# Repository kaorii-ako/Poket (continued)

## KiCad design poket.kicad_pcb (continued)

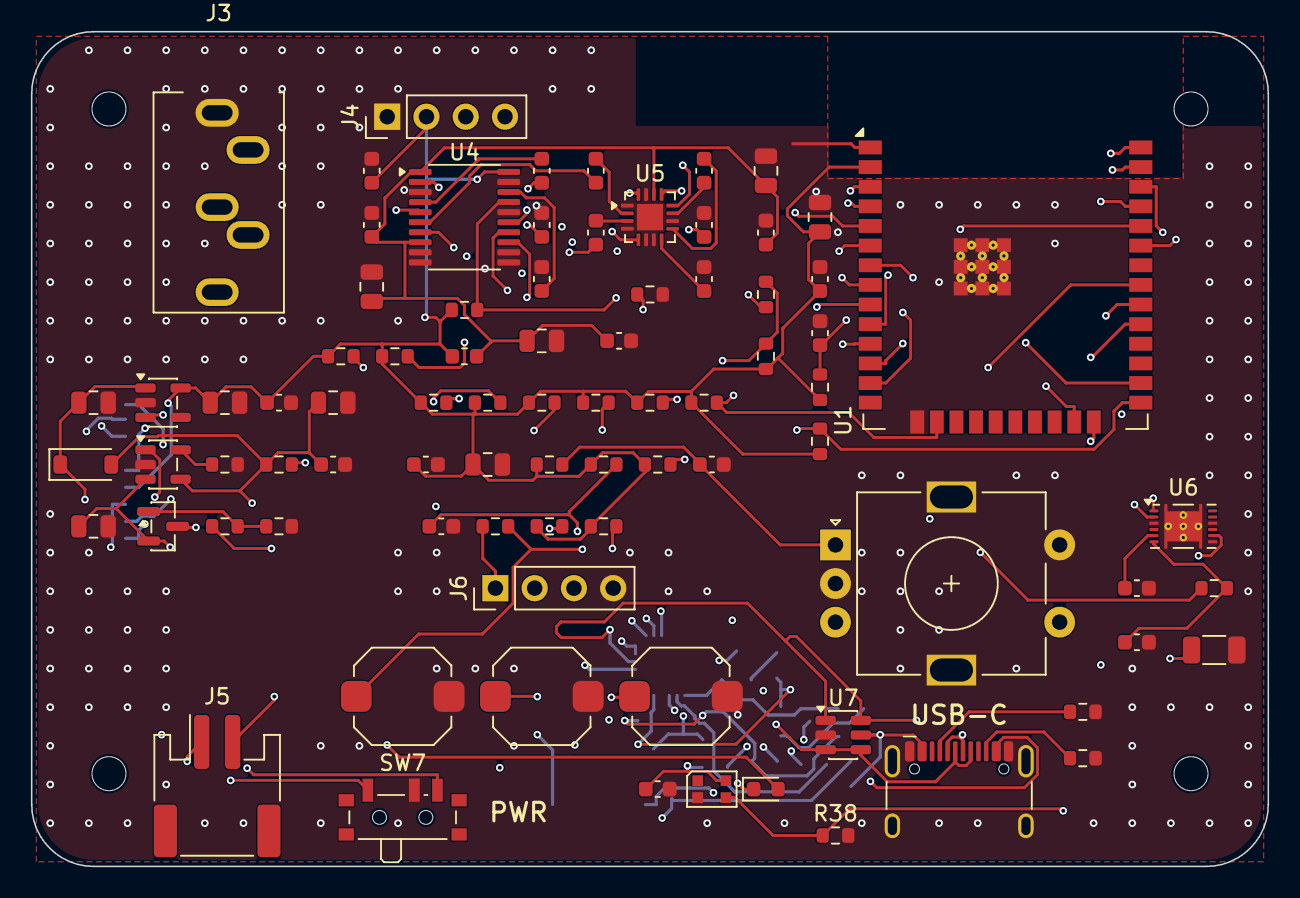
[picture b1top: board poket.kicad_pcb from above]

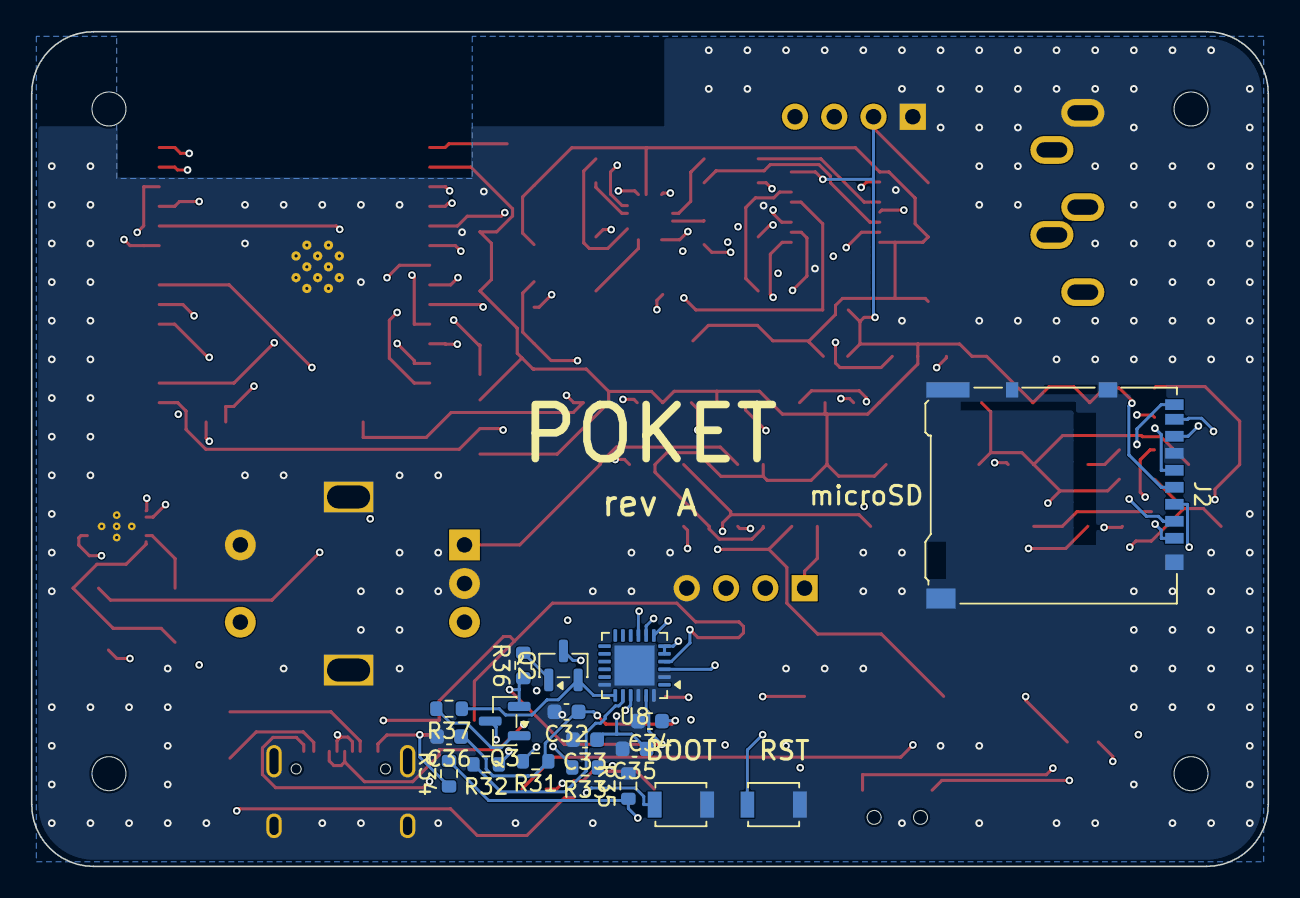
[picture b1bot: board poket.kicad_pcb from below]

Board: 4 copper layers, 80.0 x 54.0 mm, 104 parts (18 on the bottom side), 67 nets.

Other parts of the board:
MH1, MH2, MH3, MH4: MountingHole_2.2mm

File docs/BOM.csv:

Section,Ref,Qty,Value,MPN,Package,Description,Est unit USD,Est ext USD
MCU,U1,1,ESP32-WROOM-32E-N16R2,ESP32-WROOM-32E-N16R2,SMD module,Dual-core MCU + Classic BT/BLE/WiFi radio 16MB flash 2MB in-package PSRAM,3.80,3.80
Audio,U4,1,PCM5102A,PCM5102APWR,TSSOP-20,I2S stereo DAC internal PLL no MCLK needed,2.20,2.20
Audio,U5,1,PAM8908,PAM8908JER,QFN-16 3x3 EP,Stereo headphone amp charge-pump ground-centred output,0.60,0.60
Audio,J3,1,3.5mm TRS,SJ1-3535NG,THT horizontal,3.5mm stereo jack with switched tip for plug detect,0.60,0.60
Power,U2,1,MCP73831-2-OT,MCP73831T-2ACI/OT,SOT-23-5,Single-cell LiPo charger 500mA set by R3,0.65,0.65
Power,U3,1,AP2112K-3.3,AP2112K-3.3TRG1,SOT-23-5,3.3V 600mA LDO with enable,0.20,0.20
Power,U6,1,BQ27441-G1,BQ27441DRZR-G1A,SON-12 2x4mm,Coulomb-counting fuel gauge I2C,2.80,2.80
Power,Q1,1,DMG2301L,DMG2301L,SOT-23,P-channel MOSFET load-share switch,0.20,0.20
Power,D3,1,B5819W,B5819WS,SOD-123,Schottky diode USB-to-VSYS path,0.05,0.05
Power,U7,1,USBLC6-2SC6,USBLC6-2SC6,SOT-23-6,USB ESD protection array,0.25,0.25
Storage,J2,1,microSD,DM3AT-SF-PEJM5,SMD push-push,microSD socket with card-detect switch,1.00,1.00
UI,SW1,1,EC11E,EC11E15244A3,THT vertical H20mm,Rotary encoder with push switch,0.45,0.45
UI,SW2-SW4,3,Tact 6x6x5,TS-1187A-B-A-B,SMD 6x6x5mm,Transport buttons prev/play/next,0.10,0.30
UI,SW5-SW6,2,Tact 3.9x2.9,B3U-1000P,SMD,BOOT and RESET on the underside,0.15,0.30
UI,SW7,1,Slide SPDT,PCM12SMTR,SMD,Power slide switch drives the LDO enable,0.30,0.30
UI,D1,1,WS2812B-2020,WS2812B-2020,PLCC-4 2x2mm,Addressable RGB status LED,0.15,0.15
UI,D2,1,LED green,KT-0603G,0603,Charge status LED,0.03,0.03
Connectors,J1,1,USB-C,HC-TYPE-C-16P-01A,SMD 16P,USB-C receptacle USB 2.0,0.30,0.30
Connectors,J5,1,JST-PH 2pin,S2B-PH-SM4-TB,SMD horizontal,Battery connector,0.15,0.15
Connectors,J4,1,Header 1x4,Generic 2.54mm,THT,OLED module connection,0.05,0.05
Connectors,J6,1,Header 1x4,Generic 2.54mm,THT,UART debug header,0.05,0.05
Passives,FB1,1,600R@100MHz,Generic 0603,0603,Ferrite bead isolating the 3V3A analog rail,0.03,0.03
Passives,C1;C3-C5;C7;C9;C13;C16;C25,9,10uF,Generic X5R 0805 16V,0805,Bulk decoupling,0.03,0.27
Passives,C2;C6;C8;C10;C12;C14;C15;C26-C29,11,100nF,Generic X7R 0603 25V,0603,Bypass,0.01,0.11
Passives,C11;C18-C24,8,1uF,Generic X7R 0603 16V,0603,Charge-pump and coupling caps,0.02,0.16
Passives,C17,1,2.2uF,Generic X7R 0603 16V,0603,DAC charge-pump flying cap,0.02,0.02
Passives,C30;C31,2,10nF,Generic X7R 0603 50V,0603,Encoder RC filter,0.01,0.02
Passives,R1;R2,2,5.1k,Generic 0603 1%,0603,USB-C CC pulldowns,0.01,0.02
Passives,R3,1,2k,Generic 0603 1%,0603,Charge current program 500mA,0.01,0.01
Passives,R4;R23,2,1k,Generic 0603 1%,0603,LED series and fuel-gauge BAT filter,0.01,0.02
Passives,R5;R7;R8;R11-R19;R25-R30,18,10k,Generic 0603 1%,0603,Pull-ups and pull-downs,0.01,0.18
Passives,R6,1,1M,Generic 0603 1%,0603,Load-share gate pulldown,0.01,0.01
Passives,R9;R10,2,4.7k,Generic 0603 1%,0603,I2C pull-ups,0.01,0.02
Passives,R20-R22,3,100k,Generic 0603 1%,0603,Jack detect and battery divider,0.01,0.03
Passives,R24,1,0.01R,Generic 1206 1% 1W,1206,Fuel-gauge sense resistor,0.10,0.10
Off-board,BT1,1,LiPo 402535 400mAh,Generic 402535,4x25x35mm,Single-cell LiPo with protection,5.00,5.00
Off-board,DS1,1,OLED 0.96in I2C,SSD1306 128x64 module,27.3x27.8mm,Display module 4-pin I2C,3.00,3.00
Fabrication,-,1,PCB,JLCPCB 4-layer 80x54mm,1.6mm,Qty 5 minimum order incl shipping,20.00,20.00
Fabrication,-,4,M2 heat-set insert,M2x4mm OD3.2,brass,Front shell bosses,0.10,0.40
Fabrication,-,4,M2x12 screw,M2x12 pan head,steel,Back-to-front fastening,0.05,0.20
Fabrication,-,1,Filament,PETG or PLA,~25g,Three printed parts,1.00,1.00
USB,U8,1,CP2102N-A02-GQFN24,CP2102N-A02-GQFN24,QFN-24 4x4,USB-UART bridge with internal 3V3 regulator,1.85,1.85
USB,Q2 Q3,2,MMBT3904,MMBT3904,SOT-23,NPN auto-reset pair driven from DTR/RTS,0.04,0.08
USB,R34,1,22.1k,RC0603FR-0722K1L,0603,VBUS sense divider top (datasheet Fig 2.5),0.01,0.01
USB,R35,1,47.5k,RC0603FR-0747K5L,0603,VBUS sense divider bottom,0.01,0.01
USB,R31,1,1k,RC0603FR-071KL,0603,CP2102N RSTb pull-up to VIO,0.01,0.01
USB,R32,1,1k,RC0603FR-071KL,0603,Series into the bridge RXD,0.01,0.01
USB,R33,1,10k,RC0603FR-0710KL,0603,Holds the ESP RXD idle high when the bridge is unpowered,0.01,0.01
USB,R36 R37,2,10k,RC0603FR-0710KL,0603,Auto-reset base resistors,0.01,0.02
USB,R38,1,10k,RC0603FR-0710KL,0603,GPIO2 strap pull-down,0.01,0.01
USB,C32 C35,2,4.7uF,CL10A475KO8NNNC,0603,Bridge bulk bypass one per power pin,0.03,0.06
USB,C33 C34 C36,3,100nF,CL10B104KB8NNNC,0603,Bridge HF bypass one per power pin,0.01,0.03

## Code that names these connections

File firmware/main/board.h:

// Poket board pin map.
//
// Every number here was pulled out of poket.kicad_sch with
//   kicad-cli sch export netlist --format kicadxml
// rather than typed from memory. If the schematic moves, re-export and fix
// this file; nothing else in the firmware should hard-code a GPIO.
//
// REV B: the module changed from ESP32-S3-WROOM-1 to ESP32-WROOM-32E-R2.
// The S3 has Bluetooth LE only - no BR/EDR - so A2DP source, which is the
// whole point of "sends to Bluetooth headphones", could never have worked on
// it. The classic ESP32 in the -32E-R2 keeps its 2 MB PSRAM in-package, so
// unlike a WROVER it does not eat GPIO16/17 to get it.
#pragma once

#define POKET_FW_VERSION "0.2.0"
#include "driver/gpio.h"

// ---- rotary encoder (EC11, detented, with push) -------------------------
#define PIN_ENC_A        GPIO_NUM_32
#define PIN_ENC_B        GPIO_NUM_33
#define PIN_ENC_SW       GPIO_NUM_35     // input-only: needs the board's 10k

// ---- transport buttons, all active low ---------------------------------
// GPIO34/36/39 are input-only and have NO internal pull-ups, so R20-R22 on
// the board are not optional the way they were on the S3.
#define PIN_BTN_PREV     GPIO_NUM_34
#define PIN_BTN_PLAY     GPIO_NUM_36
#define PIN_BTN_NEXT     GPIO_NUM_39

// ---- I2S to the PCM5102A -----------------------------------------------
// No MCLK line exists: the DAC runs off its internal PLL from BCK/LRCK.
// Configuring an MCLK pin here would be a silent bug - there is no trace.
#define PIN_I2S_BCK      GPIO_NUM_26
#define PIN_I2S_LRCK     GPIO_NUM_25
#define PIN_I2S_DIN      GPIO_NUM_27
#define PIN_DAC_XSMT     GPIO_NUM_14     // soft mute, high = unmuted

// ---- I2C: SSD1306 OLED + BQ27441 fuel gauge ----------------------------
#define PIN_I2C_SDA      GPIO_NUM_21
#define PIN_I2C_SCL      GPIO_NUM_22
#define I2C_ADDR_OLED    0x3C
#define I2C_ADDR_GAUGE   0x55

// ---- microSD over SPI ---------------------------------------------------
// NOT the SDMMC peripheral. On the classic ESP32, slot 1 is hard-wired to
// GPIO12 for DAT2, and GPIO12 is MTDI - the flash voltage strap. A microSD
// card's internal pull-up on DAT2 holds it high at reset, which tells the
// bootloader the flash is 1.8 V and bricks the boot. SPI costs bandwidth
// nobody here needs: 320 kbps audio is 40 kB/s and the Wi-Fi link is the
// bottleneck on uploads regardless.
#define PIN_SD_SCK       GPIO_NUM_18
#define PIN_SD_MISO      GPIO_NUM_19
#define PIN_SD_MOSI      GPIO_NUM_23
#define PIN_SD_CS        GPIO_NUM_5
#define PIN_SD_CD        GPIO_NUM_13     // low = card present
#define SD_SPI_HOST      SPI2_HOST       // HSPI
#define SD_SPI_HZ        (20 * 1000 * 1000)

// ---- misc ---------------------------------------------------------------
#define PIN_AMP_EN       GPIO_NUM_4      // PAM8908 enable, high = on
#define PIN_JACK_DET     GPIO_NUM_15     // low = plug inserted
#define PIN_LED_DIN      GPIO_NUM_2      // WS2812B-2020, single pixel

// Strapping pins and what this board does about them:
//   GPIO0  BOOT button, pulled up. Also driven by the CP2102N auto-reset pair.
//   GPIO2  WS2812 data. Idles low, which is what the strap wants. Safe.
//   GPIO12 MTDI / flash voltage. LEFT UNCONNECTED - see the microSD note.
//   GPIO15 MTDO / boot-log enable, internal pull-up. Jack detect pulls it low
//          when a plug is in, so booting with headphones plugged in is silent
//          on U0TXD. Cosmetic only.
// GPIO6-11 are the module's SPI flash and are not brought out.
// There is no battery-sense divider: ADC1 is fully consumed by the encoder
// and buttons, and the BQ27441 reports voltage and current over I2C anyway.

#define BATT_FULL_MV         4200
#define BATT_EMPTY_MV        3300
